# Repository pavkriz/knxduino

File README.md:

# KNXduino - KNX bus compatible DIY device based on STM32G071 MCU with Arduino flavour

## Testing Boards

* DEPRECATED (will be replaced by STM32G0 Nucleo board): [Nucleo-F303RE](https://www.st.com/en/evaluation-tools/nucleo-f303re.html)
    * Connections:
        * KNX RX voltage divider 33k:2k -> PB0 (COMP4_INP)
        * PB1 (COMP4_OUT) -> PA6 (TIM3_CH1)
        * PA7 (TIM3_CH2) -> TX MOSFET (shorting 68R to GND, 10k pull-down on gate)
        * KNX- <-> GND

* [KNXduino One](hw-design/knxduino-one/)
    * Note: make sure to connect NRST along with SWO, SWD and GND to ST-LINK while using OpenOCD

## Development Environment

Testing IDE: [Visual Studio Code](https://code.visualstudio.com/) + [Arduino plugin](https://marketplace.visualstudio.com/items?itemName=vsciot-vscode.vscode-arduino) + [Cortex-Debug plugin](https://marketplace.visualstudio.com/items?itemName=marus25.cortex-debug)

or [Arduino IDE 1.8.5](https://www.arduino.cc/en/main/software).

Testing Arduino Core: Additional URL https://github.com/stm32duino/BoardManagerFiles/raw/master/STM32/package_stm_index.json version 1.6.1

"Blink via KNX" sketch currently compiles to approx. 28072 bytes of Flash (without bootloader, size-optimized, without hard-coded addresses, no EEPROM emulation thus not configurable at all yet). Sketch consumes approx. 4mA while powered from KNX bus without any power optimizations. Bootloader is currently approx. 9kB. Thus perfectly OK for 128kB devices.

### Development Environment for Bootloader

Use Atollic TrueSTUDIO for STM32

## Steps to compile application (sketch)

* Use [KNXduino library](https://github.com/pavkriz/knxduino-library)
* Copy `hardware` folder to your sketches folder (eg. `~/Arduino`)
* Select `KNXdunino` board, and `KNXduino Nucleo F303RE with 32kB bootloader` in your IDE (eg. vscode or Arduino IDE)
* Select `U(S)ART support: Enable (no generic 'Serial')`
* Optional: Select `Optimize` menu according to your preferences

## Known issues in vscode

* Fix hardcoded `arduinoPath` path in `.vscode/c_cpp_properties.json` file
* ~~Fix hardcoded `cortex-debug.openocdPath` path in `.vscode/settings.json` file~~ build OpenOCD and install in PATH (see below)
* Fix hardcoded `cortex-debug.armToolchainPath` path in `.vscode/settings.json` file
* Fix hardcoded path to `st_nucleo_g0.cfg` in `.vscode/launch.json` file
* `Arduino: Upload` command does not work because of `output` option in `.vscode/arduino.json` file. Use `Arduino: Verify` followed by `Debug: Continue (F5)` instead.

Note on building OpenOCD for STM32G0: 
* `git clone --recurse-submodules https://repo.or.cz/openocd.git`
* patch http://openocd.zylin.com/gitweb?p=openocd.git;a=patch;h=dcec354bfc756c4a4e1034c9461b5d3f4e55a63e
* `./bootstrap`
* `./configure --disable-werror`
* `make`
* make sure you've uninstalled package-managed openocd from system (`sudo apt-get remove openocd`)
* `sudo make install`

## Steps to compile bootloader

Use Atollic TrueSTUDIO for STM32, open and build `bootloader` project.

## TODO

* ? Migrate to PlatformIO.org when it will fully support official ST's STM32duino Core (which we use here). PlatformIO.org has much better build and dependency management (configurable preprocessor defines, local references to particular Arduino Core, libraries,...). Watch https://github.com/platformio/platform-ststm32/issues/76

## Acknowledgement

* This project is based on [Selfbus project](http://www.selfbus.org).
* This work is supported by [hkfree.org](http://www.hkfree.org) community network.

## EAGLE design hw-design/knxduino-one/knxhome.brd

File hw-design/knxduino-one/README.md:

# KNXduino One board

Custom board with STM32G071 LQFP32 MCU that fits into a [Italtronic Cbox Int H19 KNX
](https://eng.italtronic.com/products/cbox_int_en/cbox_int_h19_knx_en/) box

# Schematic

# Board

# Demo

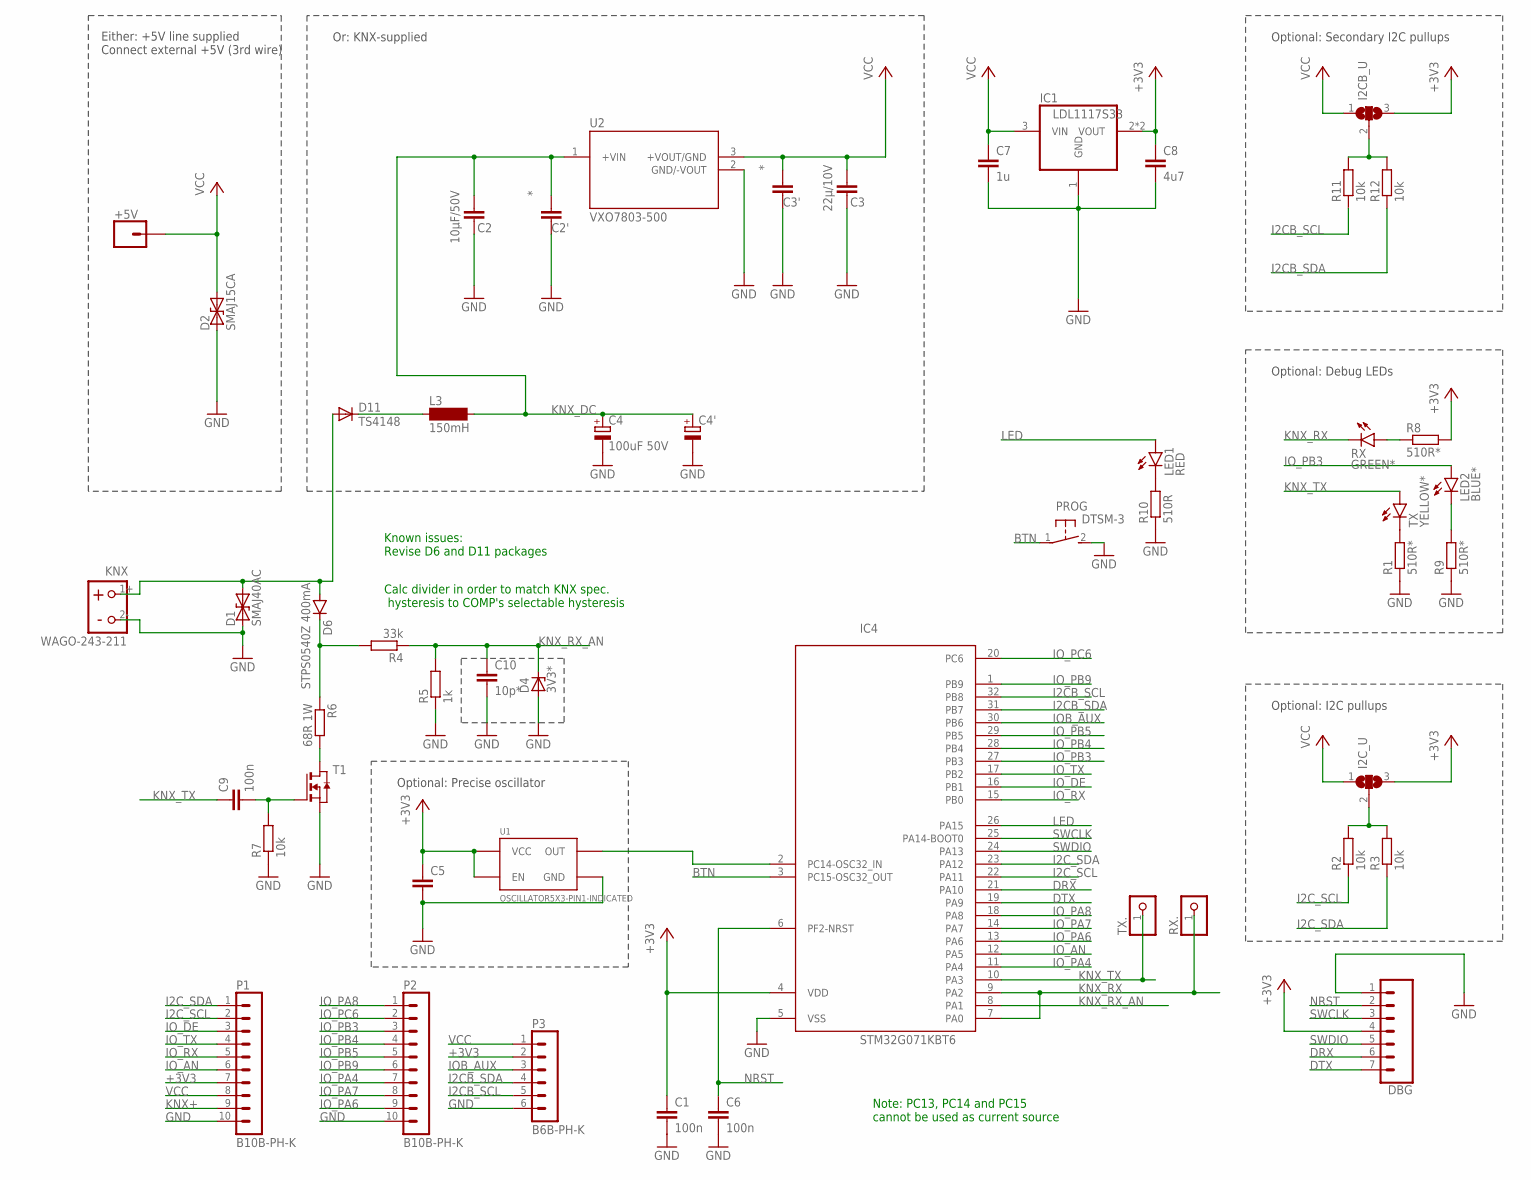
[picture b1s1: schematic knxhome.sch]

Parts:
+5V: CONN_01PTH_LONGPAD; 1X01_LONGPAD
C1, C6, C9: 100n; C0805
C2: 10µF/50V; C1210
C2', C3': *; C1210
C3: 22µ/10V; C1210
C4: 100uF 50V; E3,5-8
C4': CPOL-EU153CLV-0810; 153CLV-0810
C5: C-EUC0805; C0805
C7: 1u; C0805
C8: 4u7; C0805
C10: 10p*; C0805
D1: SMAJ40AC; DO-214AC
D2: SMAJ15CA; DO-214AC
D4: 3V3*; SOT23
D6: STPS0540Z 400mA; SOD123
D11: TS4148; SOD123
DBG: CONN_07LOCK; 1X07_LOCK
I2CB_U, I2C_U: SJ2W; SJ_2
IC1: LDL1117S33; SOT223
IC4: STM32G071KBT6; LQFP32
KNX: WAGO-243-211
L3: 150mH; BS11_LIEGEND
LED1: RED; CHIPLED_1206
LED2: BLUE*; CHIPLED_1206
P1, P2: B10B-PH-K
P3: B6B-PH-K
PROG: DTSM-3
R1, R8, R9: 510R*; R0805
R2, R3, R7, R11, R12: 10k; R0805
R4: 33k; R0805
R5: 1k; R0805
R6: 68R 1W; R2512
R10: 510R; R0805
RX: GREEN*; CHIPLED_1206
RX.: PINHD-1X1; 1X01
T1: NMOSSOT23; SOT-23
TX: YELLOW*; CHIPLED_1206
TX.: PINHD-1X1; 1X01
U1: OSCILLATOR5X3-PIN1-INDICATED; CRYSTAL-OSC-SMD-5X3
U2: VXO7803-500; CONV_VXO7803-500

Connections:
+3V3: C1.1, C5.1, C8.1, DBG.4, I2CB_U.3, I2C_U.3, IC1.2 (VOUT), IC1.4 (VOUT), IC4.4 (VDD), P1.7, P3.2, R8.2, U1.1 (EN), U1.4 (VCC)
BTN: IC4.3 (PC15-OSC32_OUT), PROG.1
DRX: DBG.6, IC4.21 (PA10)
DTX: DBG.7, IC4.19 (PA9)
GND: C1.2, C2.1, C2'.1, C3.1, C3'.1, C4.-, C4'.-, C5.2, C6.2, C7.2, C8.2, C10.2, D1.A, D2.A, D4.1 (A), DBG.1, IC1.1 (GND), IC4.5 (VSS), KNX.2-, P1.10, P2.10, P3.6, PROG.2, R1.1, R5.1, R7.1, R9.1, R10.1, T1.2 (S), U1.2 (GND), U2.2 (GND/-VOUT)
I2CB_SCL: IC4.32 (PB8), P3.5, R11.1
I2CB_SDA: IC4.31 (PB7), P3.4, R12.1
I2C_PUP: I2C_U.2, R2.2, R3.2
I2C_PUP1: I2CB_U.2, R11.2, R12.2
I2C_SCL: IC4.22 (PA11), P1.2, R2.1
I2C_SDA: IC4.23 (PA12), P1.1, R3.1
IOB_AUX: IC4.30 (PB6), P3.3
IO_AN: IC4.12 (PA5), P1.6
IO_DE: IC4.16 (PB1), P1.3
IO_PA4: IC4.11 (PA4), P2.7
IO_PA6: IC4.13 (PA6), P2.9
IO_PA7: IC4.14 (PA7), P2.8
IO_PA8: IC4.18 (PA8), P2.1
IO_PB3: IC4.27 (PB3), LED2.A, P2.3
IO_PB4: IC4.28 (PB4), P2.4
IO_PB5: IC4.29 (PB5), P2.5
IO_PB9: IC4.1 (PB9), P2.6
IO_PC6: IC4.20 (PC6), P2.2
IO_RX: IC4.15 (PB0), P1.5
IO_TX: IC4.17 (PB2), P1.4
KNX+: D1.C, D6.A, D11.A, KNX.1+, P1.9
KNX_DC: C2.2, C2'.2, C4.+, C4'.+, L3.2, U2.1 (+VIN)
KNX_RECT: D6.C, R4.2, R6.1
KNX_RX: IC4.7 (PA0), IC4.9 (PA2), RX.C, RX..1
KNX_RX_AN: C10.1, D4.3 (C), IC4.8 (PA1), R4.1, R5.2
KNX_TX: C9.1, IC4.10 (PA3), TX.A, TX..1
LED: IC4.26 (PA15), LED1.A
unnamed: D11.C, L3.1
unnamed: LED1.C, R10.2
unnamed: R1.2, TX.C
unnamed: R8.1, RX.A
unnamed: LED2.C, R9.2
unnamed: R6.2, T1.1 (D)
unnamed: C9.2, R7.2, T1.3 (G)
NRST: C6.1, DBG.2, IC4.6 (PF2-NRST)
OSC: IC4.2 (PC14-OSC32_IN), U1.3 (OUT)
SWCLK: DBG.3, IC4.25 (PA14-BOOT0)
SWDIO: DBG.5, IC4.24 (PA13)
VCC: +5V.1, C3.2, C3'.2, C7.1, D2.C, I2CB_U.1, I2C_U.1, IC1.3 (VIN), P1.8, P3.1, U2.3 (+VOUT/GND)

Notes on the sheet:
Calc divider in order to match KNX spec. hysteresis to COMP's selectable hysteresis
Known issues: Revise D6 and D11 packages
Or: KNX-supplied
Either: +5V line supplied Connect external +5V (3rd wire)
Note: PC13, PC14 and PC15 cannot be used as current source
Optional: Debug LEDs
Optional: Secondary I2C pullups
Optional: I2C pullups
Optional: Precise oscillator

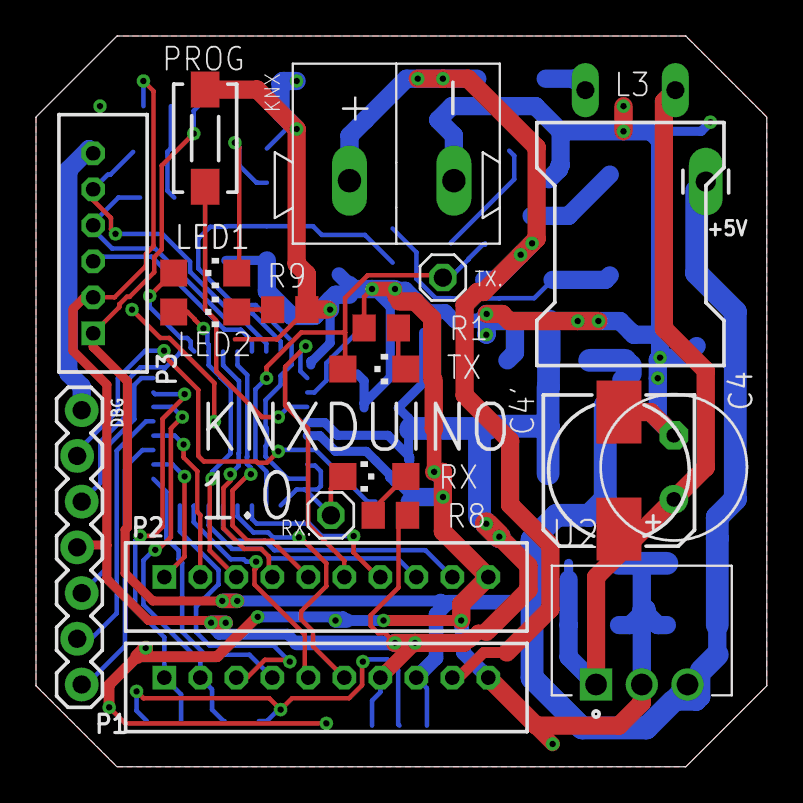
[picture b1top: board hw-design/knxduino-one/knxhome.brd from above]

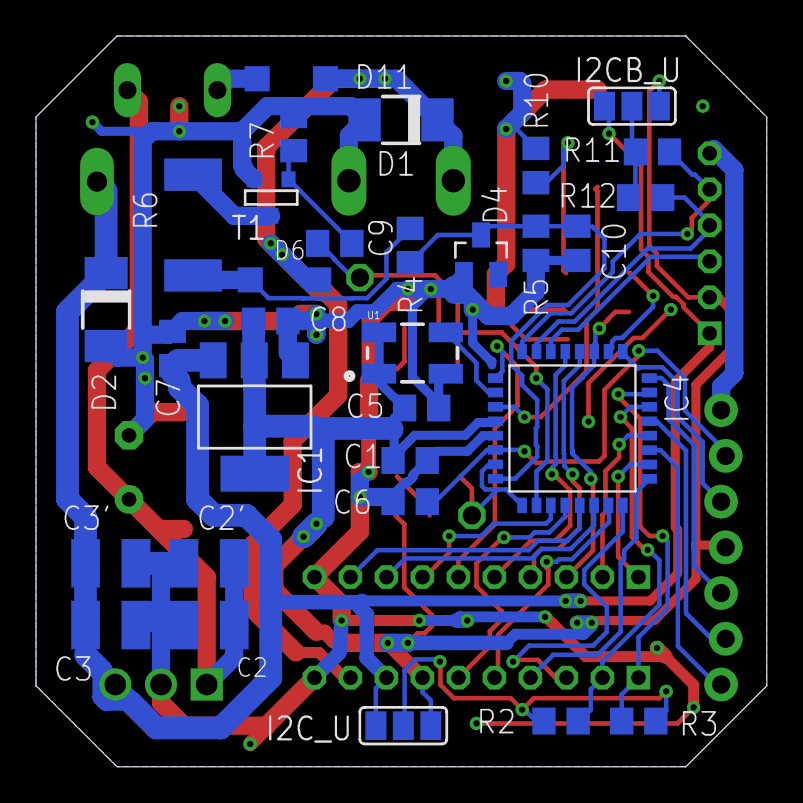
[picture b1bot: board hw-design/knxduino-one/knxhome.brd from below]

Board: 2 copper layers, 40.6 x 40.6 mm, 51 parts (31 on the bottom side), 44 nets.

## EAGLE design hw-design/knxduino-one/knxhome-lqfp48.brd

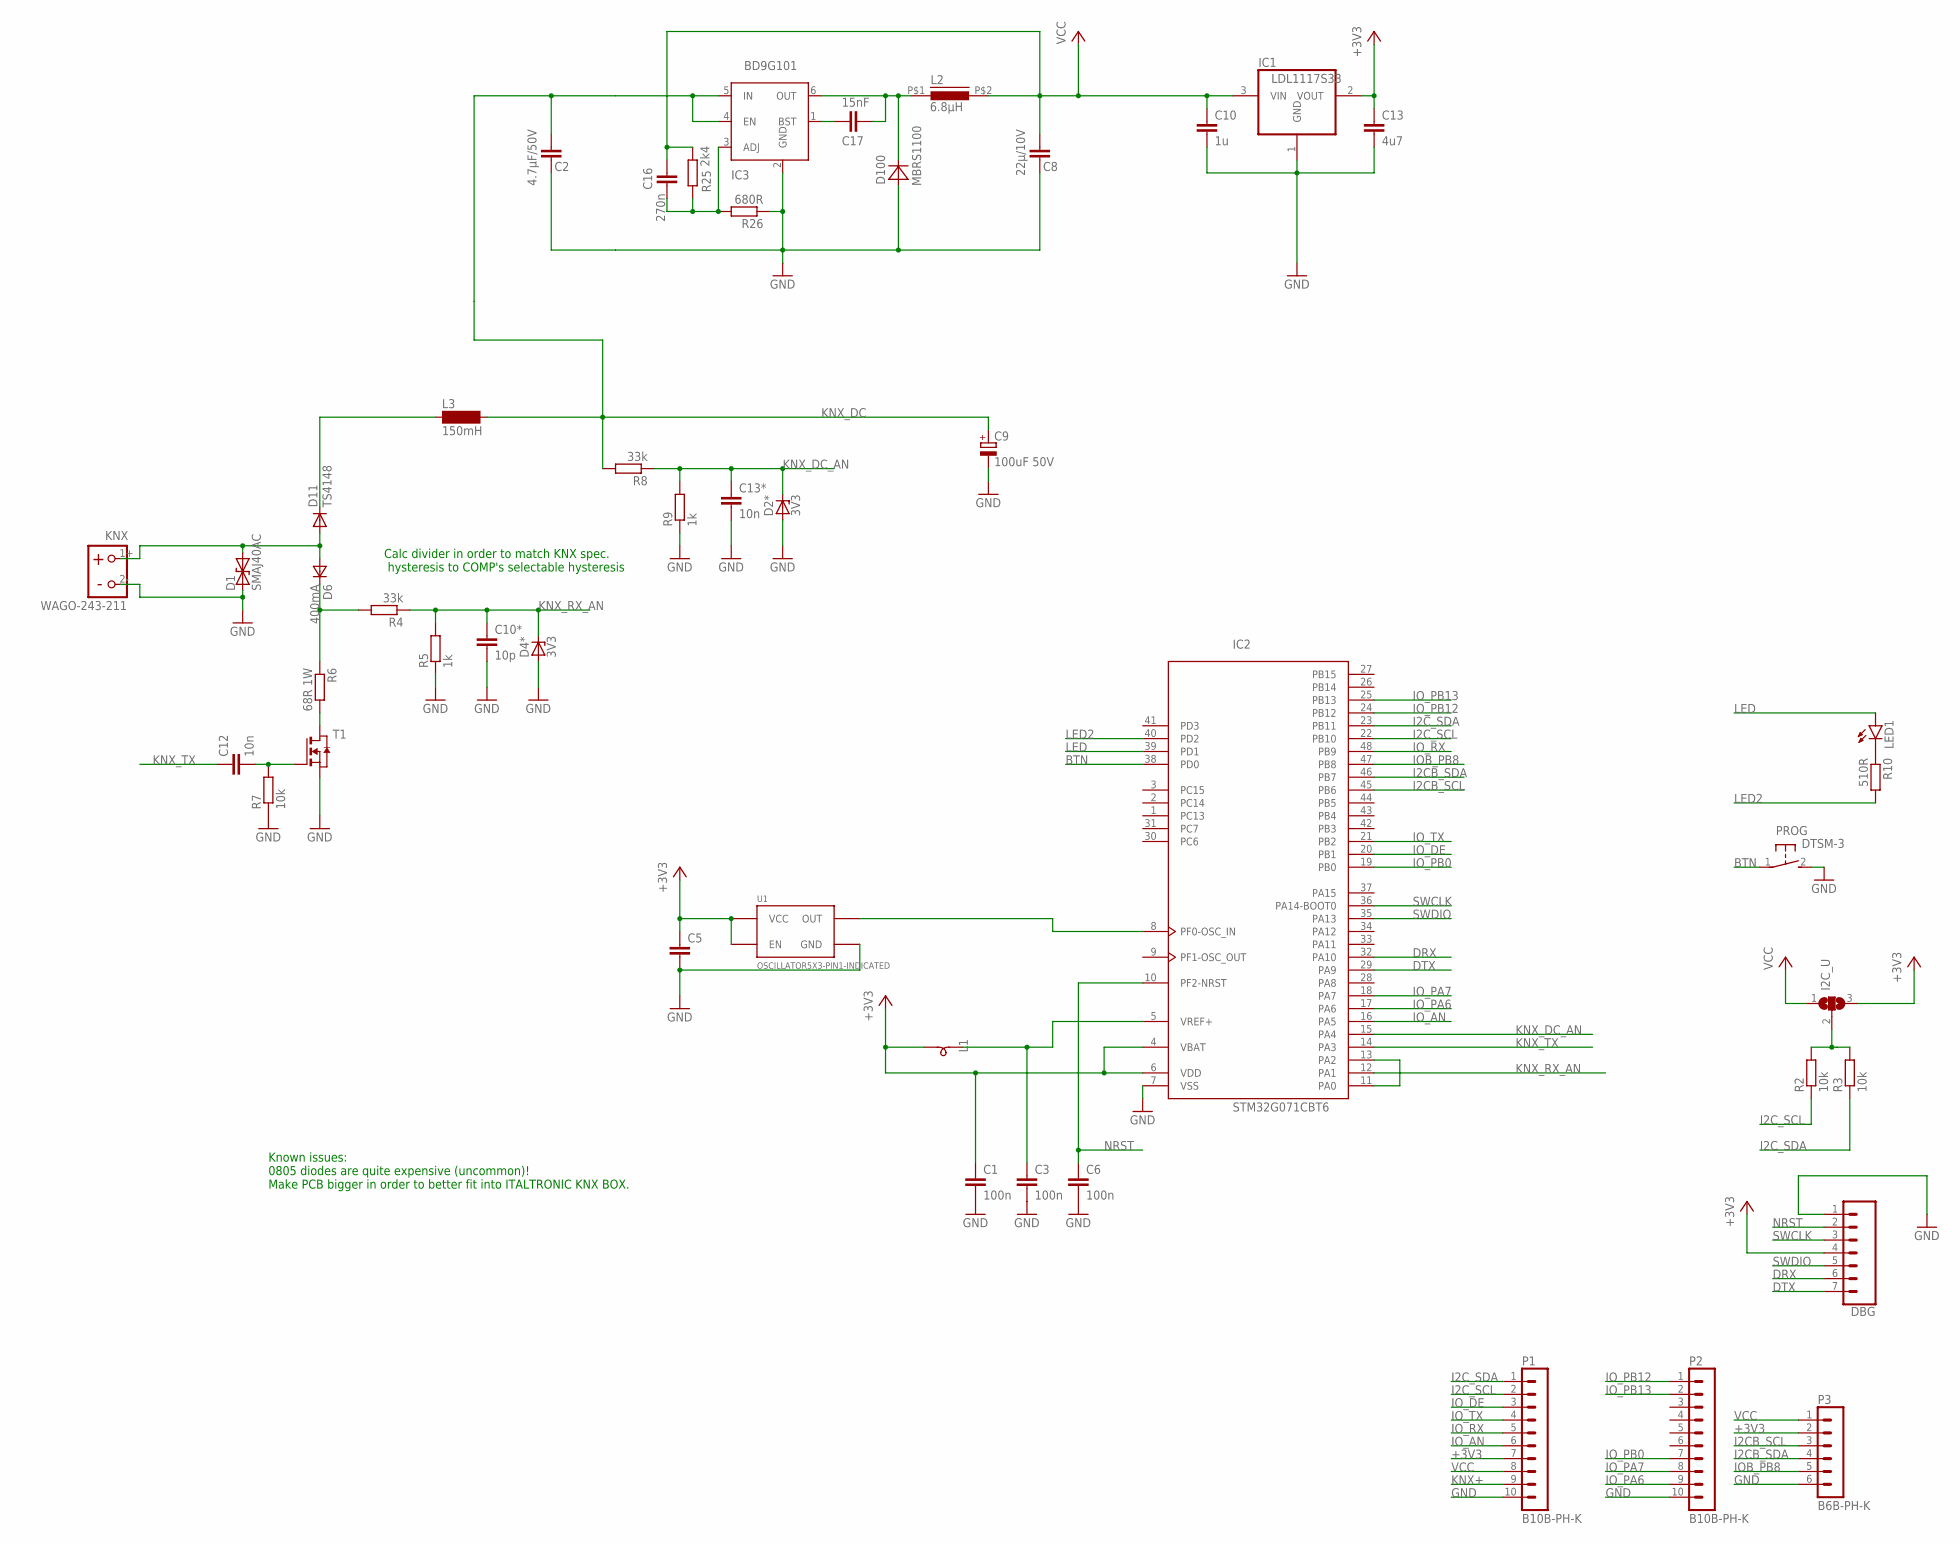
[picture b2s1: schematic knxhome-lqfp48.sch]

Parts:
C1, C3, C6: 100n; C0805
C2: 4.7µF/50V; C0805
C5: C-EUC0805; C0805
C8: 22µ/10V; C0805
C9: 100uF 50V; E3,5-8
C10: 1u; C0805
C10*: 10p; C0805
C12, C13*: 10n; C0805
C13: 4u7; C0805
C16: 270n; C0805
C17: 15nF; C0805
D1: SMAJ40AC; DO-214AC
D2*, D4*: 3V3; SOT23
D6: 400mA; SOD323
D11: TS4148; D0805
D100: MBRS1100; SMA
DBG: CONN_07LOCK; 1X07_LOCK
I2C_U: SJ2W; SJ_2
IC1: LDL1117S33; SOT223
IC2: STM32G071CBT6; LQFP48
IC3: BD9G101; SOT23-6
KNX: WAGO-243-211
L1: FERRITE BEAD; SM-B5
L2: 6.8µH; PIS2812
L3: 150mH; BS11_LIEGEND
LED1: LEDCHIP-LED0805; CHIP-LED0805
P1, P2: B10B-PH-K
P3: B6B-PH-K
PROG: DTSM-3
R2, R3, R7: 10k; R0805
R4, R8: 33k; R0805
R5, R9: 1k; R0805
R6: 68R 1W; R2512
R10: 510R; R0805
R25: 2k4; R0805
R26: 680R; R0805
T1: NMOSSOT23; SOT-23
U1: OSCILLATOR5X3-PIN1-INDICATED; CRYSTAL-OSC-SMD-5X3

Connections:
+3V3: C1.1, C5.1, C13.1, DBG.4, I2C_U.3, IC1.2 (VOUT), IC2.4 (VBAT), IC2.6 (VDD), L1.1, P1.7, P3.2, U1.1 (EN), U1.4 (VCC)
ADJ: C16.1, IC3.3 (ADJ), R25.1, R26.2
BTN: IC2.38 (PD0), PROG.1
DRX: DBG.6, IC2.32 (PA10)
DTX: DBG.7, IC2.29 (PA9)
GND: C1.2, C2.1, C3.2, C5.2, C6.2, C8.1, C9.-, C10.2, C10*.2, C13.2, C13*.2, D1.A, D2*.1 (A), D4*.1 (A), D100.A, DBG.1, IC1.1 (GND), IC2.7 (VSS), IC3.2 (GND), KNX.2-, P1.10, P2.10, P3.6, PROG.2, R5.1, R7.1, R9.1, R26.1, T1.2 (S), U1.2 (GND)
I2CB_SCL: IC2.45 (PB6), P3.3
I2CB_SDA: IC2.46 (PB7), P3.4
I2C_PUP: I2C_U.2, R2.2, R3.2
I2C_SCL: IC2.22 (PB10), P1.2, R2.1
I2C_SDA: IC2.23 (PB11), P1.1, R3.1
IOB_PB8: IC2.47 (PB8), P3.5
IO_AN: IC2.16 (PA5), P1.6
IO_DE: IC2.20 (PB1), P1.3
IO_PA6: IC2.17 (PA6), P2.9
IO_PA7: IC2.18 (PA7), P2.8
IO_PB0: IC2.19 (PB0), P2.7
IO_PB12: IC2.24 (PB12), P2.1
IO_PB13: IC2.25 (PB13), P2.2
IO_RX: IC2.48 (PB9), P1.5
IO_TX: IC2.21 (PB2), P1.4
KNX+: D1.C, D6.2 (A), D11.A, KNX.1+, P1.9
KNX_DC: C2.2, C9.+, IC3.4 (EN), IC3.5 (IN), L3.2, R8.2
KNX_DC_AN: C13*.1, D2*.3 (C), IC2.15 (PA4), R8.1, R9.2
KNX_RECT: D6.1 (C), R4.2, R6.1
KNX_RX_AN: C10*.1, D4*.3 (C), IC2.12 (PA1), R4.1, R5.2
KNX_TX: C12.1, IC2.14 (PA3)
LED: IC2.39 (PD1), LED1.A
LED2: IC2.40 (PD2), R10.2
LX: C17.1, D100.C, IC3.6 (OUT), L2.P$1 (1)
unnamed: D11.C, L3.1
unnamed: LED1.C, R10.1
unnamed: IC2.11 (PA0), IC2.13 (PA2)
unnamed: R6.2, T1.1 (D)
unnamed: C12.2, R7.2, T1.3 (G)
unnamed: C17.2, IC3.1 (BST)
NRST: C6.1, DBG.2, IC2.10 (PF2-NRST)
OSC: IC2.8 (PF0-OSC_IN), U1.3 (OUT)
SWCLK: DBG.3, IC2.36 (PA14-BOOT0)
SWDIO: DBG.5, IC2.35 (PA13)
VCC: C8.2, C10.1, C16.2, I2C_U.1, IC1.3 (VIN), L2.P$2 (2), P1.8, P3.1, R25.2
VDDA: C3.1, IC2.5 (VREF+), L1.2

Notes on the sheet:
Calc divider in order to match KNX spec. hysteresis to COMP's selectable hysteresis
Known issues: 0805 diodes are quite expensive (uncommon)! Make PCB bigger in order to better fit into ITALTRONIC KNX BOX.

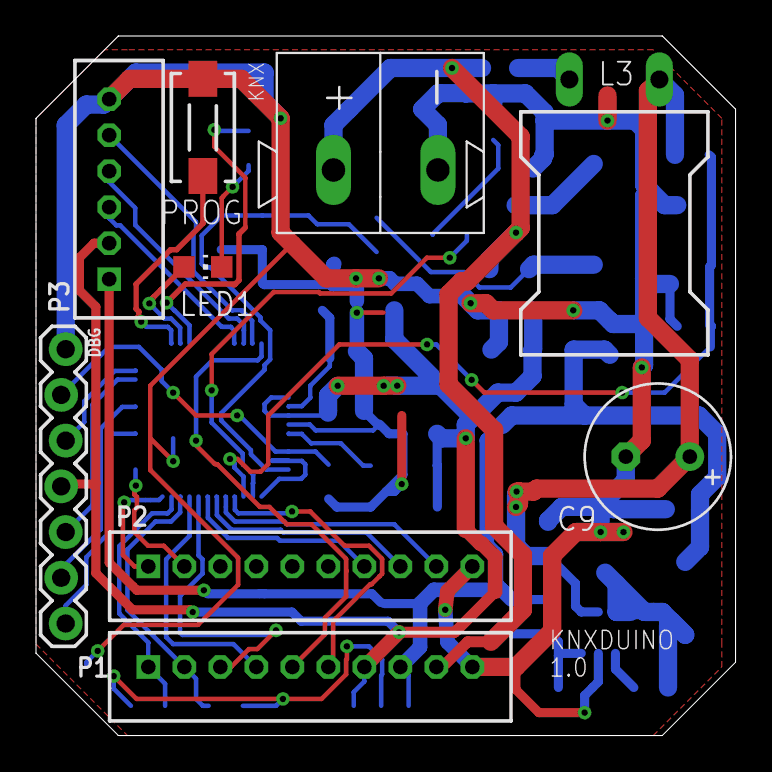
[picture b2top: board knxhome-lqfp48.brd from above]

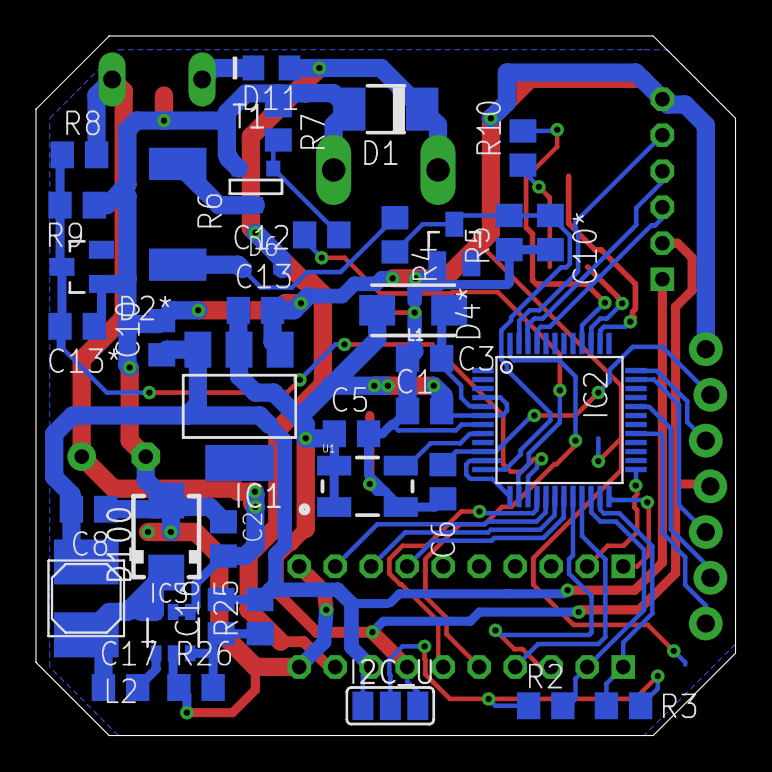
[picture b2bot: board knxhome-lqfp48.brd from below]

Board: 2 copper layers, 38.9 x 38.9 mm, 47 parts (38 on the bottom side), 42 nets.

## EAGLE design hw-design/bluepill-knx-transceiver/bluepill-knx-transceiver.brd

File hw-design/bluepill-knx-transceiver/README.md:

# Blue Pill KNX Transceiver

## Not maintained any more

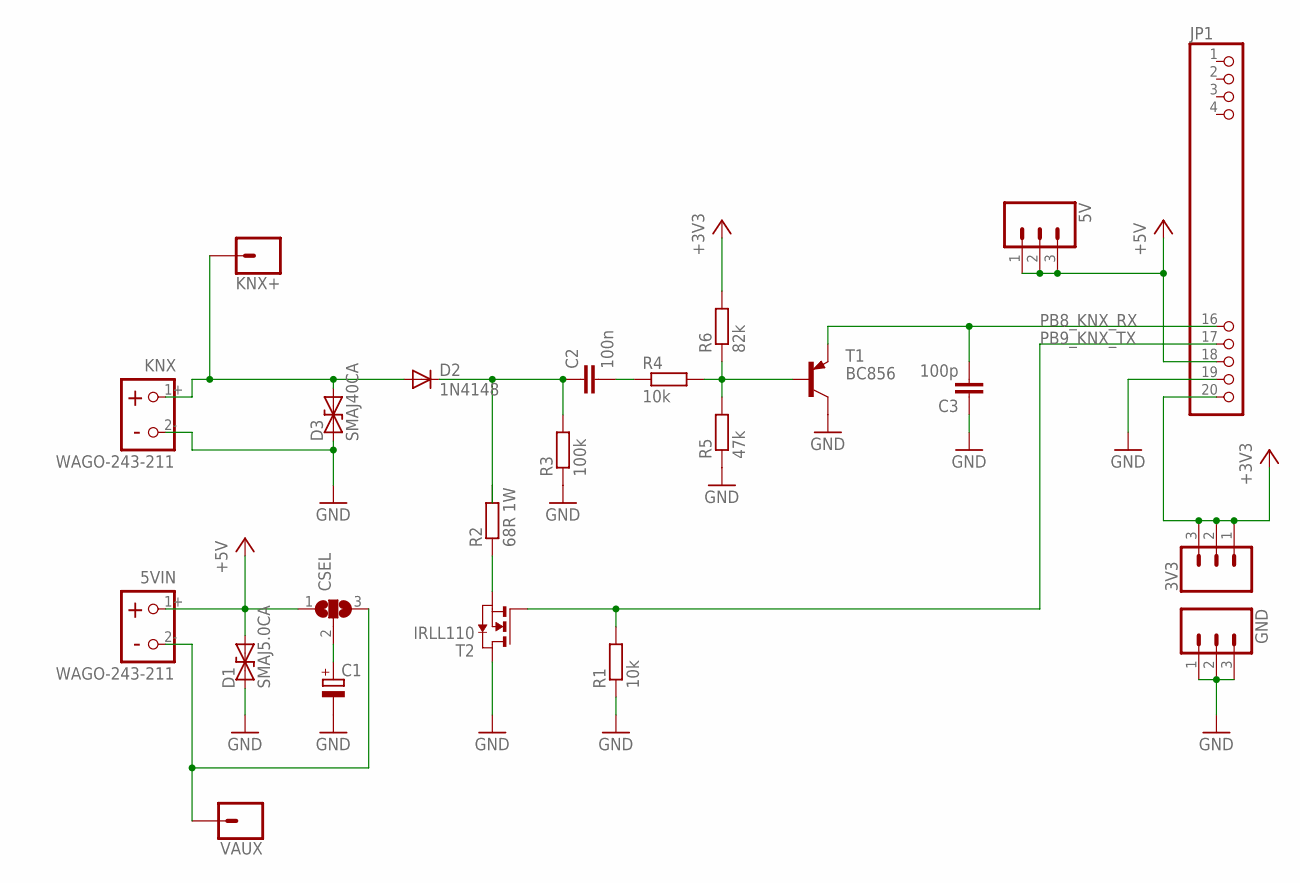
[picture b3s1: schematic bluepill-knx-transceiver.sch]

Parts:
3V3, 5V: CONN_03; 1X03
5VIN: WAGO-243-211
C1: CPOL-EUE3.5-8; E3,5-8
C2: 100n; C1206
C3: 100p; C1206
CSEL: SJ2W; SJ_2
D1: SMAJ5.0CA; DO-214AC
D2: 1N4148; MINIMELF
D3: SMAJ40CA; DO-214AC
GND: CONN_03; 1X03
JP1: PINHD-1X20-BP; 1X20-BP
KNX: WAGO-243-211
KNX+: CONN_01; 1X01
R1, R4: 10k; R1206
R2: 68R 1W; R2512
R3: 100k; R1206
R5: 47k; R1206
R6: 82k; R1206
T1: BC856; SOT23-BEC
T2: IRLL110; SOT223
VAUX: CONN_01; 1X01

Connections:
5V: 5V.1, 5V.2, 5V.3, 5VIN.1+, CSEL.1, D1.C, JP1.18
+3V3: 3V3.1, 3V3.2, 3V3.3, JP1.20, R6.2
EIB+: D2.A, D3.C, KNX.1+, KNX+.1
GND: C1.-, C3.1, D1.A, D3.A, GND.1, GND.2, GND.3, JP1.19, KNX.2-, R1.1, R3.1, R5.1, T1.C, T2.2 (D), T2.4 (D)
KNX+D: C2.1, D2.C, R2.2, R3.2
unnamed: C2.2, R4.1
unnamed: R2.1, T2.3 (S)
unnamed: C1.+, CSEL.2
unnamed: R4.2, R5.2, R6.1, T1.B
PB8_KNX_RX: C3.2, JP1.16, T1.E
PB9_KNX_TX: JP1.17, R1.2, T2.1 (G)
VAUX: 5VIN.2-, CSEL.3, VAUX.1

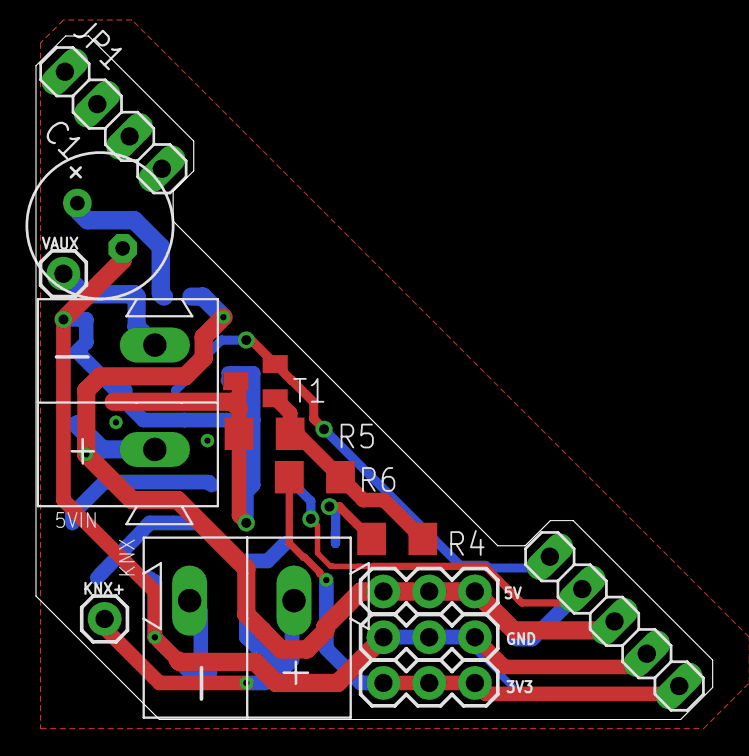
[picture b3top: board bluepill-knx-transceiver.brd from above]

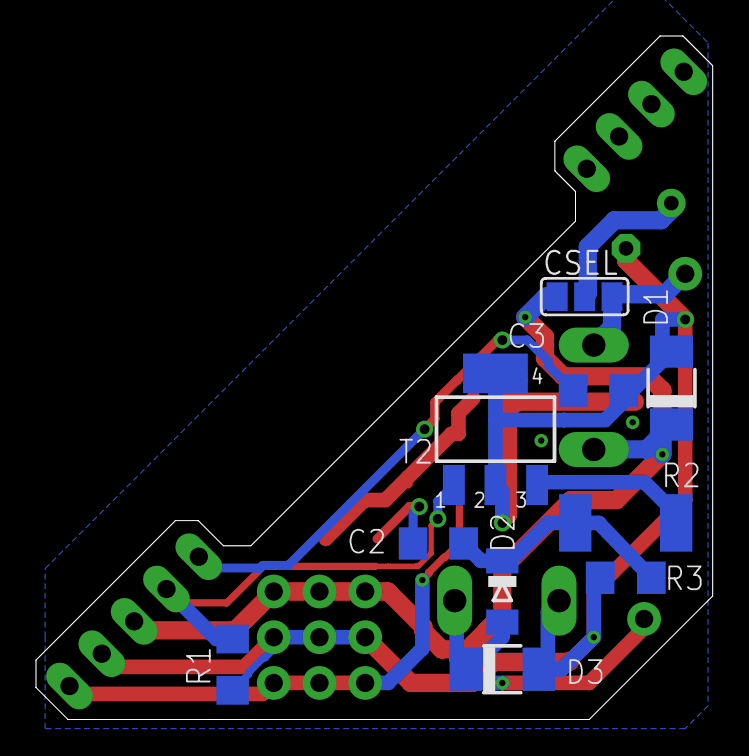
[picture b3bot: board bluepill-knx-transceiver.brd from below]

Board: 2 copper layers, 37.6 x 38.0 mm, 23 parts (10 on the bottom side), 12 nets.

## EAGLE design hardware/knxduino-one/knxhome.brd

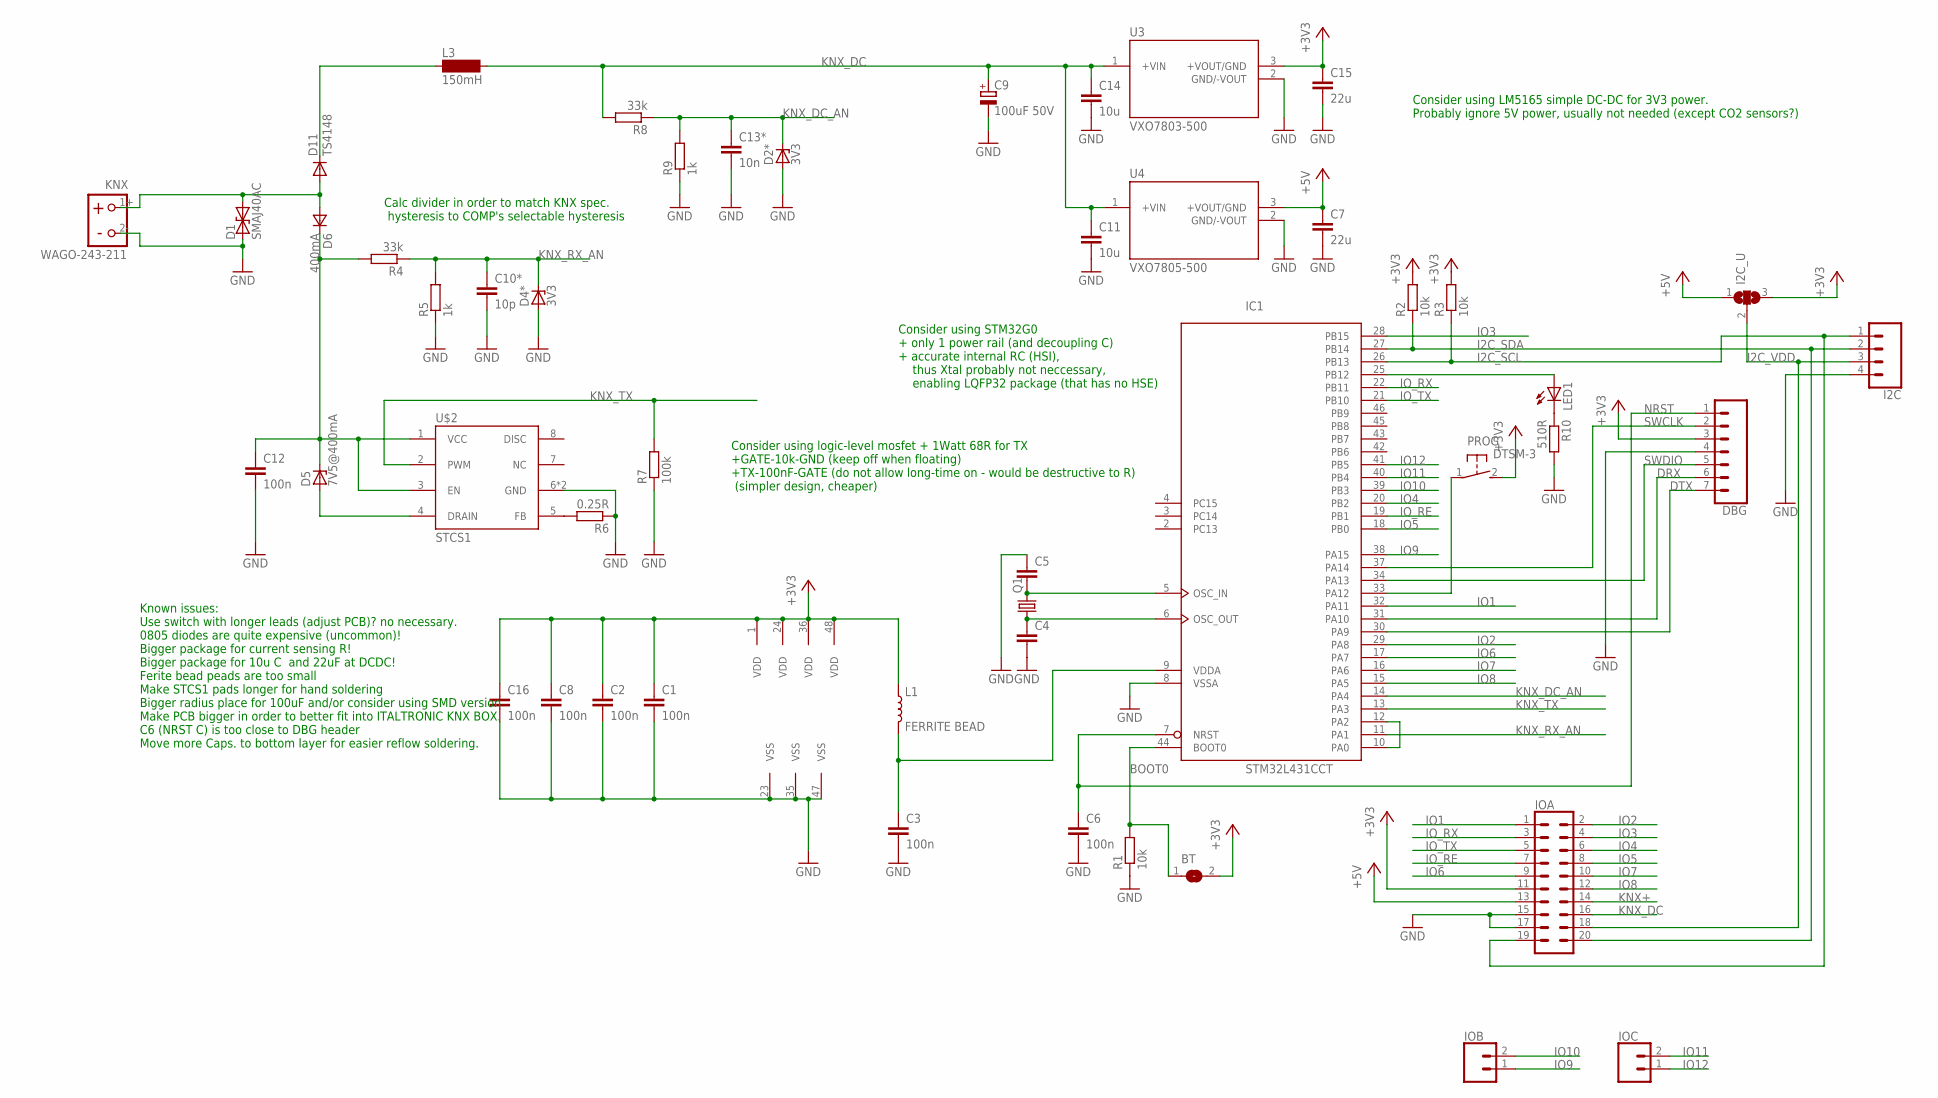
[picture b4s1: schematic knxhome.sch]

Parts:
BT: SJ
C1, C2, C3, C6, C8, C12, C16: 100n; C0805
C4, C5: C-EUC0805; C0805
C7, C15: 22u; C0805
C9: 100uF 50V; E3,5-8
C10*: 10p; C0805
C11, C14: 10u; C0805
C13*: 10n; C0805
D1: SMAJ40AC; DO-214AC
D2*, D4*: 3V3; SOT23
D5: 7V5@400mA; SMB
D6: 400mA; SOD323
D11: TS4148; D0805
DBG: CONN_07LOCK; 1X07_LOCK
I2C: CONN_04JST-PTH-VERT; JST-4-PTH-VERT
I2C_U: SJ2W; SJ_2
IC1: STM32L431CCT; LQFP48
IOA: CONN_10X2; 2X10
IOB: CONN_02; 1X02
IOC: CONN_02; 1X02
KNX: WAGO-243-211
L1: FERRITE BEAD; 0805
L3: 150mH; BS11_LIEGEND
LED1: LED3MM
PROG: DTSM-3
Q1: CRYSTALHC49S; HC49/S
R1, R2, R3: 10k; R0805
R4, R8: 33k; R0805
R5, R9: 1k; R0805
R6: 0.25R; R0805
R7: 100k; R0805
R10: 510R; R0805
U3: VXO7803-500; CONV_VXO7803-500
U4: VXO7805-500; CONV_VXO7803-500
U$2: STCS1; POWERSO-8

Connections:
+3V3: BT.2, C1.1, C2.1, C8.1, C15.1, C16.1, DBG.3, I2C_U.3, IC1.1 (VDD), IC1.24 (VDD), IC1.36 (VDD), IC1.48 (VDD), IOA.11, L1.1, PROG.2, R2.2, R3.2, U3.3 (+VOUT/GND)
+5V: C7.1, I2C_U.1, IOA.13, U4.3 (+VOUT/GND)
BOOT0: BT.1, IC1.44 (BOOT0), R1.2
BTN: IC1.33 (PA12), PROG.1
DRX: DBG.6, IC1.31 (PA10)
DTX: DBG.7, IC1.30 (PA9)
GND: C1.2, C2.2, C3.2, C4.2, C5.1, C6.2, C7.2, C8.2, C9.-, C10*.2, C11.2, C12.2, C13*.2, C14.2, C15.2, C16.2, D1.A, D2*.1 (A), D4*.1 (A), DBG.4, I2C.4, IC1.8 (VSSA), IC1.23 (VSS), IC1.35 (VSS), IC1.47 (VSS), IOA.15, IOA.17, KNX.2-, R1.1, R5.1, R6.1, R7.1, R9.1, R10.2, U3.2 (GND/-VOUT), U4.2 (GND/-VOUT), U$2.6 (GND), U$2.EX (GND)
I2C_SCL: I2C.1, IC1.26 (PB13), IOA.19, R3.1
I2C_SDA: I2C.2, IC1.27 (PB14), IOA.20, R2.1
I2C_VDD: I2C.3, I2C_U.2, IOA.18
IO1: IC1.32 (PA11), IOA.1
IO2: IC1.29 (PA8), IOA.2
IO3: IC1.28 (PB15), IOA.4
IO4: IC1.20 (PB2), IOA.6
IO5: IC1.18 (PB0), IOA.8
IO6: IC1.17 (PA7), IOA.9
IO7: IC1.16 (PA6), IOA.10
IO8: IC1.15 (PA5), IOA.12
IO9: IC1.38 (PA15), IOB.1
IO10: IC1.39 (PB3), IOB.2
IO11: IC1.40 (PB4), IOC.2
IO12: IC1.41 (PB5), IOC.1
IO_RE: IC1.19 (PB1), IOA.7
IO_RX: IC1.22 (PB11), IOA.3
IO_TX: IC1.21 (PB10), IOA.5
KNX+: D1.C, D6.2 (A), D11.A, IOA.14, KNX.1+
KNX_DC: C9.+, C11.1, C14.1, IOA.16, L3.2, R8.2, U3.1 (+VIN), U4.1 (+VIN)
KNX_DC_AN: C13*.1, D2*.3 (C), IC1.14 (PA4), R8.1, R9.2
KNX_RECT: C12.1, D5.C, D6.1 (C), R4.2, U$2.1 (VCC), U$2.3 (EN)
KNX_RX_AN: C10*.1, D4*.3 (C), IC1.11 (PA1), R4.1, R5.2
KNX_TX: IC1.13 (PA3), R7.2, U$2.2 (PWM)
LED: IC1.25 (PB12), LED1.A
unnamed: D11.C, L3.1
unnamed: R6.2, U$2.5 (FB)
unnamed: LED1.K (C), R10.1
unnamed: IC1.10 (PA0), IC1.12 (PA2)
unnamed: C4.1, IC1.6 (OSC_OUT), Q1.1
unnamed: C5.2, IC1.5 (OSC_IN), Q1.2
NRST: C6.1, DBG.1, IC1.7 (NRST)
REF: D5.A, U$2.4 (DRAIN)
SWCLK: DBG.2, IC1.37 (PA14)
SWDIO: DBG.5, IC1.34 (PA13)
VDDA: C3.1, IC1.9 (VDDA), L1.2

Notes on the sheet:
Calc divider in order to match KNX spec. hysteresis to COMP's selectable hysteresis
Known issues: Use switch with longer leads (adjust PCB)? no necessary. 0805 diodes are quite expensive (uncommon)! Bigger package for current sensing R! Bigger package for 10u C and 22uF at DCDC! Ferite bead peads are too small Make STCS1 pads longer for hand soldering Bigger radius place for 100uF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
Consider using logic-level mosfet + 1Watt 68R for TX +GATE-10k-GND (keep off when floating) +TX-100nF-GATE (do not allow long-time on - would be destructive to R) (simpler design, cheaper)
Consider using LM5165 simple DC-DC for 3V3 power. Probably ignore 5V power, usually not needed (except CO2 sensors?)
Consider using STM32G0 + only 1 power rail (and decoupling C) + accurate internal RC (HSI), thus Xtal probably not neccessary, enabling LQFP32 package (that has no HSE)

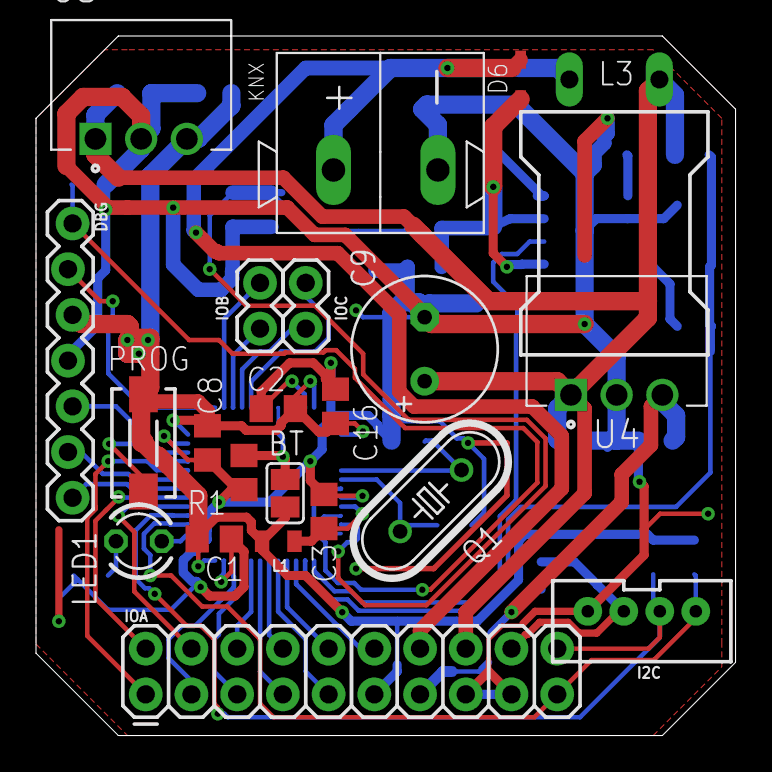
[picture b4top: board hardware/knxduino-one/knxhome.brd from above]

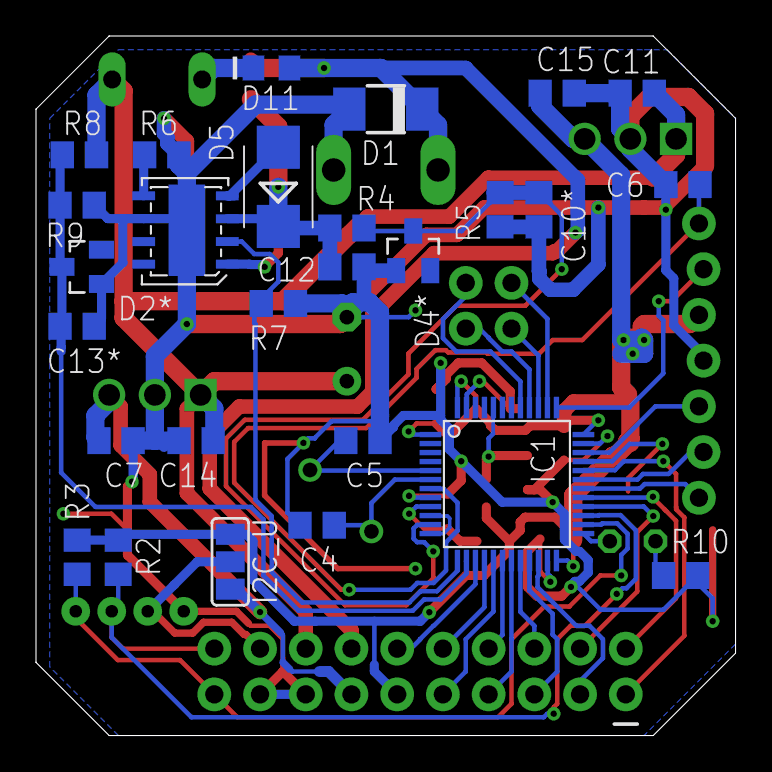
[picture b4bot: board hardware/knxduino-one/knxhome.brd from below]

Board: 2 copper layers, 38.9 x 38.9 mm, 49 parts (27 on the bottom side), 43 nets.

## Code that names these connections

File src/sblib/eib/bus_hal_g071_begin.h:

inline void BusHal::begin()
{
    // COMP init
  __HAL_RCC_GPIOA_CLK_ENABLE();
  __HAL_RCC_GPIOB_CLK_ENABLE();
    /**COMP1 GPIO Configuration    
    PA0     ------> COMP1_OUT
    PA1     ------> COMP1_INP 
    */

    GPIO_InitTypeDef GPIO_InitStruct = {0};

    GPIO_InitStruct.Pin = GPIO_PIN_1;
    GPIO_InitStruct.Mode = GPIO_MODE_ANALOG;
    GPIO_InitStruct.Pull = GPIO_NOPULL;
    HAL_GPIO_Init(GPIOA, &GPIO_InitStruct);

    GPIO_InitStruct.Pin = GPIO_PIN_0;
    GPIO_InitStruct.Mode = GPIO_MODE_AF_PP;
    GPIO_InitStruct.Pull = GPIO_NOPULL;
    GPIO_InitStruct.Speed = GPIO_SPEED_FREQ_LOW;
    GPIO_InitStruct.Alternate = GPIO_AF7_COMP1;
    HAL_GPIO_Init(GPIOA, &GPIO_InitStruct);

    // tmp TODO
    
    // // PB1     ------> COMP1_INM 
    // GPIO_InitStruct.Pin = GPIO_PIN_1;
    // GPIO_InitStruct.Mode = GPIO_MODE_ANALOG;
    // GPIO_InitStruct.Pull = GPIO_NOPULL;
    // HAL_GPIO_Init(GPIOB, &GPIO_InitStruct);

    hcomp.Instance = COMP1;
    hcomp.Init.InputPlus = COMP_INPUT_PLUS_IO3;
    //hcomp.Init.InputMinus = COMP_INPUT_MINUS_IO1; // TMP TODO
    hcomp.Init.InputMinus = COMP_INPUT_MINUS_DAC1_CH1;// TMP TODO
    hcomp.Init.OutputPol = COMP_OUTPUTPOL_NONINVERTED;
    hcomp.Init.WindowOutput = COMP_WINDOWOUTPUT_EACH_COMP;
    hcomp.Init.Hysteresis = COMP_HYSTERESIS_HIGH;   // 30mV
    hcomp.Init.BlankingSrce = COMP_BLANKINGSRC_NONE;
    hcomp.Init.Mode = COMP_POWERMODE_HIGHSPEED;
    hcomp.Init.WindowMode = COMP_WINDOWMODE_DISABLE;
    hcomp.Init.TriggerMode = COMP_TRIGGERMODE_NONE;
    if (HAL_COMP_Init(&hcomp) != HAL_OK)
    {
      Error_Handler();
    }

    if (HAL_COMP_Start(&hcomp) != HAL_OK) {
      Error_Handler();
    }

    // tmp 

    // GPIO_InitStruct.Pin = GPIO_PIN_2;
    // GPIO_InitStruct.Mode = GPIO_MODE_INPUT;
    // GPIO_InitStruct.Pull = GPIO_NOPULL;
    // GPIO_InitStruct.Speed = GPIO_SPEED_FREQ_LOW;
    // HAL_GPIO_Init(GPIOA, &GPIO_InitStruct);

    // TIM init

    // Arduino interfacing for UPDATE event callback that is already handled by Arduino STM32 core,
    // beware, may interfere with libraries using STM32 hardware timers (PWM, Servo, SoftSerial,...)
    _timer.timer = TIM15;
    // mimics TimerHandleInit:
    TIM_HandleTypeDef *htim = &(_timer.handle);

    // HAL stuff
    __HAL_RCC_TIM15_CLK_ENABLE();
  
    /**TIM15 GPIO Configuration    
    PA2     ------> TIM15_CH1 
    */
    GPIO_InitStruct.Pin = GPIO_PIN_2;
    GPIO_InitStruct.Mode = GPIO_MODE_AF_PP;
    GPIO_InitStruct.Pull = GPIO_NOPULL;
    GPIO_InitStruct.Speed = GPIO_SPEED_FREQ_LOW;
    GPIO_InitStruct.Alternate = GPIO_AF5_TIM15;
    HAL_GPIO_Init(GPIOA, &GPIO_InitStruct);

    /**TIM15 GPIO Configuration    
    PA3     ------> TIM15_CH2 
    */
    GPIO_InitStruct.Pin = GPIO_PIN_3;
    GPIO_InitStruct.Mode = GPIO_MODE_AF_PP;
    GPIO_InitStruct.Pull = GPIO_NOPULL;
    GPIO_InitStruct.Speed = GPIO_SPEED_FREQ_LOW;
    GPIO_InitStruct.Alternate = GPIO_AF5_TIM15;
    HAL_GPIO_Init(GPIOA, &GPIO_InitStruct);

    HAL_NVIC_EnableIRQ(TIM15_IRQn);

    htim->Instance = TIM15;
    htim->Init.Prescaler = 64; // 64MHz/64 = 1MHz (ie. 1us tick) TODO calc base on real CLK
    htim->Init.CounterMode = TIM_COUNTERMODE_UP;
    htim->Init.Period = 65535; // 2^16-1
    htim->Init.ClockDivision = TIM_CLOCKDIVISION_DIV1;
    htim->Init.RepetitionCounter = 0;
    htim->Init.AutoReloadPreload = TIM_AUTORELOAD_PRELOAD_DISABLE;
    if (HAL_TIM_Base_Init(htim) != HAL_OK) {
        _Error_Handler(__FILE__, __LINE__);
    }
    if (HAL_TIM_IC_Init(htim) != HAL_OK)
    {
      Error_Handler();
    }
    if (HAL_TIM_PWM_Init(htim) != HAL_OK)
    {
      Error_Handler();
    }

    TIM_IC_InitTypeDef sConfigIC;
    TIM_OC_InitTypeDef sConfigOC;

    sConfigIC.ICPolarity = TIM_INPUTCHANNELPOLARITY_FALLING;
    sConfigIC.ICSelection = TIM_ICSELECTION_DIRECTTI;
    sConfigIC.ICPrescaler = TIM_ICPSC_DIV1;
    sConfigIC.ICFilter = 4;
    if (HAL_TIM_IC_ConfigChannel(htim, &sConfigIC, TIM_CHANNEL_1) != HAL_OK)
    {
      Error_Handler();
    }
    sConfigOC.OCMode = TIM_OCMODE_PWM1;
    sConfigOC.Pulse = 0;
    sConfigOC.OCPolarity = TIM_OCPOLARITY_LOW;
    sConfigOC.OCNPolarity = TIM_OCNPOLARITY_HIGH;
    sConfigOC.OCFastMode = TIM_OCFAST_DISABLE;
    sConfigOC.OCIdleState = TIM_OCIDLESTATE_RESET;
    sConfigOC.OCNIdleState = TIM_OCNIDLESTATE_RESET;
    if (HAL_TIM_PWM_ConfigChannel(htim, &sConfigOC, TIM_CHANNEL_2) != HAL_OK)
    {
      Error_Handler();
    }
    // the stupid HAL_TIM_PWM_ConfigChannel automaticaly enables TIM_CCMR1_OC2PE preload bit, but we dont want to use it
    htim->Instance->CCMR1 &= ~TIM_CCMR1_OC2PE;  // disable TIM_CCMR1_OC2PE
    
    if (HAL_TIM_Base_Start(htim) != HAL_OK) {
      Error_Handler();
    }

    if (HAL_TIM_IC_Start_IT(htim, TIM_CHANNEL_1) != HAL_OK) {
      Error_Handler();
    }
    // TODO? make sure we don't make any unintentional pulse here
    if (HAL_TIM_PWM_Start(htim, TIM_CHANNEL_2) != HAL_OK) {
      Error_Handler();
    }
}

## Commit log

2018-07-08 blink test on Nucleo STM32F303RE
2018-07-08 short readme
2018-07-08 unify include path in c_cpp_properties
2018-07-08 fix ELF path
2018-07-08 readme known issues
2018-07-08 Comparator init and necessary tweaks
2018-07-08 fix markdown typo
2018-07-16 comparator is up and running
2018-08-09 bluepill knx transceiver
2018-08-09 transceiver board GND fills
2018-08-12 prepared for DCDC
2018-08-12 knxduino-one board
2018-08-12 object oriented low level func wrapper
2018-08-12 original selfbus eib bus class
2018-08-26 receiver proof-of-concept
    receiving working except the first telegram and it's ACK
    COMP threshold generated by DAC is a fixed voltage
    (not following DC BUS voltage)
2018-08-26 readme reference to selfbus
2018-08-26 cleanups
2018-08-26 fix duplicate busHal.begin() call
2018-08-26 BCU integration proof-of-concept
    still, the first telegram is always malformed and sometimes some later ones as well,
    most of the received telegrams are OK
2018-08-27 fix receiving first telegram after startup
2018-09-02 transmitter working
2018-09-11 Switching to STM32L4 LQFP48, new TX and RX design
2019-02-24 Some HW notes after first physical PCBs were made
2019-02-28 STM32G071 LQFP48 version
2019-04-13 Bootloader RX,TX working, IAP not yet
2019-04-13 STM32G0 LQFP32 HW initial design
2019-04-15 empty updater project
2019-04-15 original updater
2019-04-15 Modified updater with calimero-core deps and customized MC
2019-04-25 Bootloader+Updater 1st working prototype
2019-04-26 Sketch reallocated after the bootloader, arduino board definition reworked
2019-05-31 Diff engine for Updater
2019-06-10 STM32G071 LQFP32 design v1.0
2019-06-10 Diff engine for Updater optimization - use whole Flash as possible src
2019-06-10 Two Nucleo F303 variants - with and without bootloader
2019-06-10 Serial TX buffer in order to avoid blocking prints
2019-06-10 Fix tmp missing KNX src address in application
2019-06-11 HW files cleanup and image previews
2019-06-11 Schematic more compact
2019-06-11 Top and bot. board values presets, values adjusted
2019-07-10 First working STM32G0 firmware
2019-07-11 Readme updates, demo GIF
2019-07-11 cleanup
2019-07-11 Library moved to pavkriz/knxduino-library repo
2019-11-05 Bootloader with diff-support and STM32G0 support
2020-02-14 Fix diff updater, bootloader, reset to bootloader

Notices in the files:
parts and their libraries:
SparkFun-Connectors: Licensing: Creative Commons ShareAlike 4.0 International - https://creativecommons.org/licenses/by-sa/4.0
con-jst-ph: Copyright (C) 2016, Bob Starr
